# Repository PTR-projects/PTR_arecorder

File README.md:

# Arecorder - Open Source Flight Data Recorder

**Version:** v2.2 (PTR edition)  
**Maintained by:** bartekM  

A compact, high-g flight data recorder designed specifically for model and amateur rocketry. The Arecorder logs 3-axis acceleration and orientation data to an SD card during launch, ascent, apogee, and recovery. Developed and used by the **Polskie Towarzystwo Rakietowe (PTR)** – the Polish Rocketry Society.

This repository contains all **design files** needed to build your own Arecorder: KiCad schematics & PCB layout, Gerber files, Bill of Materials (BOM), assembly notes, and firmware source code.

- **Original forum thread** (Polish/English discussion): [forum.rakiety.org.pl/viewtopic.php?t=3039](https://forum.rakiety.org.pl/viewtopic.php?t=3039)
- **PTR Discord** (support & community)

---

## Features

- High-range 3-axis accelerometer:
  - Primary: **MMA6827** (±120 g)
  - Alternative: **H3LIS331** (with adapter board, higher availability and better specs)
- On-board SD card slot for raw flight data logging
- Improved firmware with better calibration accuracy and write reliability
- Compact design suitable for most model rockets (fits standard payload bays)
- Easy post-flight analysis (data saved in simple format)
- Open-source hardware & firmware – build it yourself or modify it

---

---

## Quick Start

1. **Order PCBs** – use the Gerbers in `hardware/gerbers/` (any PCB manufacturer, e.g. JLCPCB, PCBWay).
2. **Buy components** – see `hardware/BOM.csv`.
3. **Assemble** – most soldering can be done by hand; complex parts can be outsourced.
4. **Flash firmware** – use MPLAB X IDE + PIC debugger.
5. **Format SD card** (FAT32) before first use.
6. **Calibrate** the accelerometer (detailed in the manual).
7. **Fly** – insert into rocket, power on, launch, retrieve data after flight.

Full assembly and usage instructions are in the original manual and `docs/assembly-guide.md`.

---

## Hardware Notes (v2.2 PTR)

- Double-layer PCB (no changes planned for this revision)
- Sensor upgrade from original MMA6519 (80 g) to MMA6827 (120 g)
- Optional H3LIS331 adapter board included in the design files

---

## License

- **Hardware designs** – [CERN Open Hardware Licence Version 2 – Strongly Reciprocal](LICENSE_hardware)  
- **Firmware & software** – [MIT LICENSE](LICENSE)
- **Documentation** – CC-BY-SA 4.0

See [LICENSE](LICENSE) file for details.

---

## Contributing

Pull requests are welcome! Whether it's:
- Bug fixes
- New features
- Better documentation
- Improved firmware

Just open an issue or PR. You can also support development via [Buy Me a Coffee](https://www.buymeacoffee.com/bartekM).

---

## Contact

- Maintainer: **bartekM** (GitHub @bartekM or PM on PTR forum/Discord)
- Community: PTR Discord server

---

**Happy flying and safe recoveries!** 🚀

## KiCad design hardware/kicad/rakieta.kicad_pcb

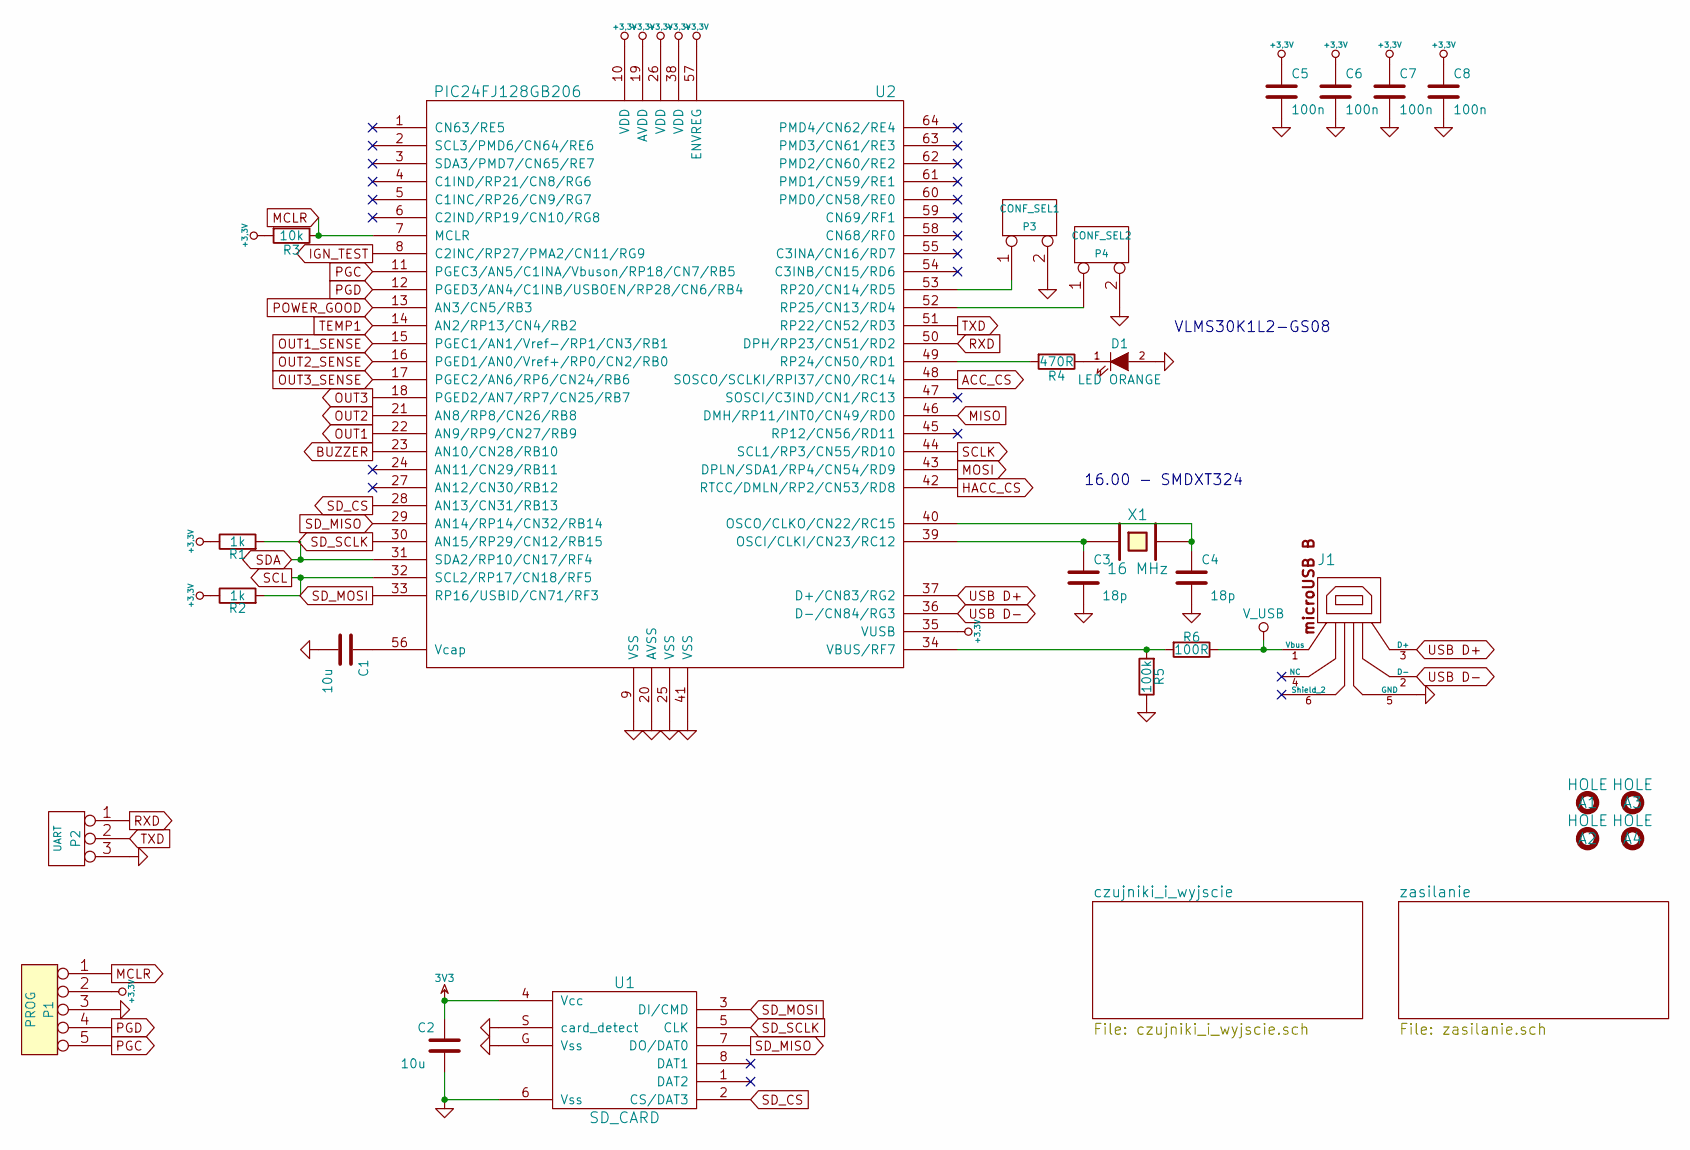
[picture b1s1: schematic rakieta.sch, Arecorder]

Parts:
A1, A2, A3, A4: HOLE; HOLE_3mm
C1, C2: 10u; SM0805
C3, C4: 18p; SM0603
C5, C6, C7, C8: 100n; SM0603
D1: LED ORANGE; SM1210_DIODE
J1: USB_B_micro; USB_MICRO
P1: PROG; conn_goldpin_5
P2: UART; conn_goldpin_3
P3: CONF_SEL1; conn_goldpin_2
P4: CONF_SEL2; conn_goldpin_2
R1, R2: 1k; SM0603
R3: 10k; SM0603
R4: 470R; SM0603
R5: 100k; SM0603
R6: 100R; SM0603
U1: SD_CARD; MICRO_SD_CARD_SLOT
U2: PIC24FJ128GB206; TQFP_64
X1: 16 MHz; HC-3.4x2.7

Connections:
3V3: C2.1, U1.4 (Vcc); also elsewhere on the board
+3.3V: C5.1, C6.1, C7.1, C8.1, P1.2, R1.1, R2.1, R3.2, U2.10 (VDD), U2.19 (AVDD), U2.26 (VDD), U2.35 (VUSB), U2.38 (VDD), U2.57 (ENVREG); also elsewhere on the board
ACC_CS: U2.48 (SOSCO/SCLKI/RPI37/CN0/RC14); also elsewhere on the board
BUZZER: U2.23 (AN10/CN28/RB10); also elsewhere on the board
GND: C1.2, C2.2, C3.2, C4.2, C5.2, C6.2, C7.2, C8.2, D1.2 (A), J1.5 (GND), P1.3, P2.3, P3.2 (PM), P4.2 (PM), R5.1, U1.6 (Vss), U1.G (Vss), U1.S (card_detect), U2.9 (VSS), U2.20 (AVSS), U2.25 (VSS), U2.41 (VSS); also elsewhere on the board
HACC_CS: U2.42 (RTCC/DMLN/RP2/CN53/RD8); also elsewhere on the board
IGN_TEST: U2.8 (C2INC/RP27/PMA2/CN11/RG9); also elsewhere on the board
MCLR: P1.1, R3.1, U2.7 (MCLR)
MISO: U2.46 (DMH/RP11/INT0/CN49/RD0); also elsewhere on the board
MOSI: U2.43 (DPLN/SDA1/RP4/CN54/RD9); also elsewhere on the board
unnamed: C1.1, U2.56 (Vcap)
unnamed: C3.1, U2.39 (OSCI/CLKI/CN23/RC12), X1.1
unnamed: C4.1, U2.40 (OSCO/CLKO/CN22/RC15), X1.2
unnamed: D1.1 (K), R4.1
unnamed: P3.1, U2.53 (RP20/CN14/RD5)
unnamed: P4.1, U2.52 (RP25/CN13/RD4)
unnamed: R4.2, U2.49 (RP24/CN50/RD1)
unnamed: R5.2, R6.2, U2.34 (VBUS/RF7)
OUT1: U2.22 (AN9/RP9/CN27/RB9); also elsewhere on the board
OUT1_SENSE: U2.15 (PGEC1/AN1/Vref-/RP1/CN3/RB1); also elsewhere on the board
OUT2: U2.21 (AN8/RP8/CN26/RB8); also elsewhere on the board
OUT2_SENSE: U2.16 (PGED1/AN0/Vref+/RP0/CN2/RB0); also elsewhere on the board
OUT3: U2.18 (PGED2/AN7/RP7/CN25/RB7); also elsewhere on the board
OUT3_SENSE: U2.17 (PGEC2/AN6/RP6/CN24/RB6); also elsewhere on the board
PGC: P1.5, U2.11 (PGEC3/AN5/C1INA/Vbuson/RP18/CN7/RB5)
PGD: P1.4, U2.12 (PGED3/AN4/C1INB/USBOEN/RP28/CN6/RB4)
POWER_GOOD: U2.13 (AN3/CN5/RB3); also elsewhere on the board
RXD: P2.1, U2.50 (DPH/RP23/CN51/RD2)
SCL: R2.2, U2.32 (SCL2/RP17/CN18/RF5); also elsewhere on the board
SCLK: U2.44 (SCL1/RP3/CN55/RD10); also elsewhere on the board
SDA: R1.2, U2.31 (SDA2/RP10/CN17/RF4); also elsewhere on the board
SD_CS: U1.2 (CS/DAT3), U2.28 (AN13/CN31/RB13)
SD_MISO: U1.7 (DO/DAT0), U2.29 (AN14/RP14/CN32/RB14)
SD_MOSI: U1.3 (DI/CMD), U2.33 (RP16/USBID/CN71/RF3)
SD_SCLK: U1.5 (CLK), U2.30 (AN15/RP29/CN12/RB15)
TEMP1: U2.14 (AN2/RP13/CN4/RB2); also elsewhere on the board
TXD: P2.2 (PM), U2.51 (RP22/CN52/RD3)
USB D+: J1.3 (D+), U2.37 (D+/CN83/RG2)
USB D-: J1.2 (D-), U2.36 (D-/CN84/RG3)
V_USB: J1.1 (Vbus), R6.1; also elsewhere on the board

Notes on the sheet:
16.00 - SMDXT324
VLMS30K1L2-GS08

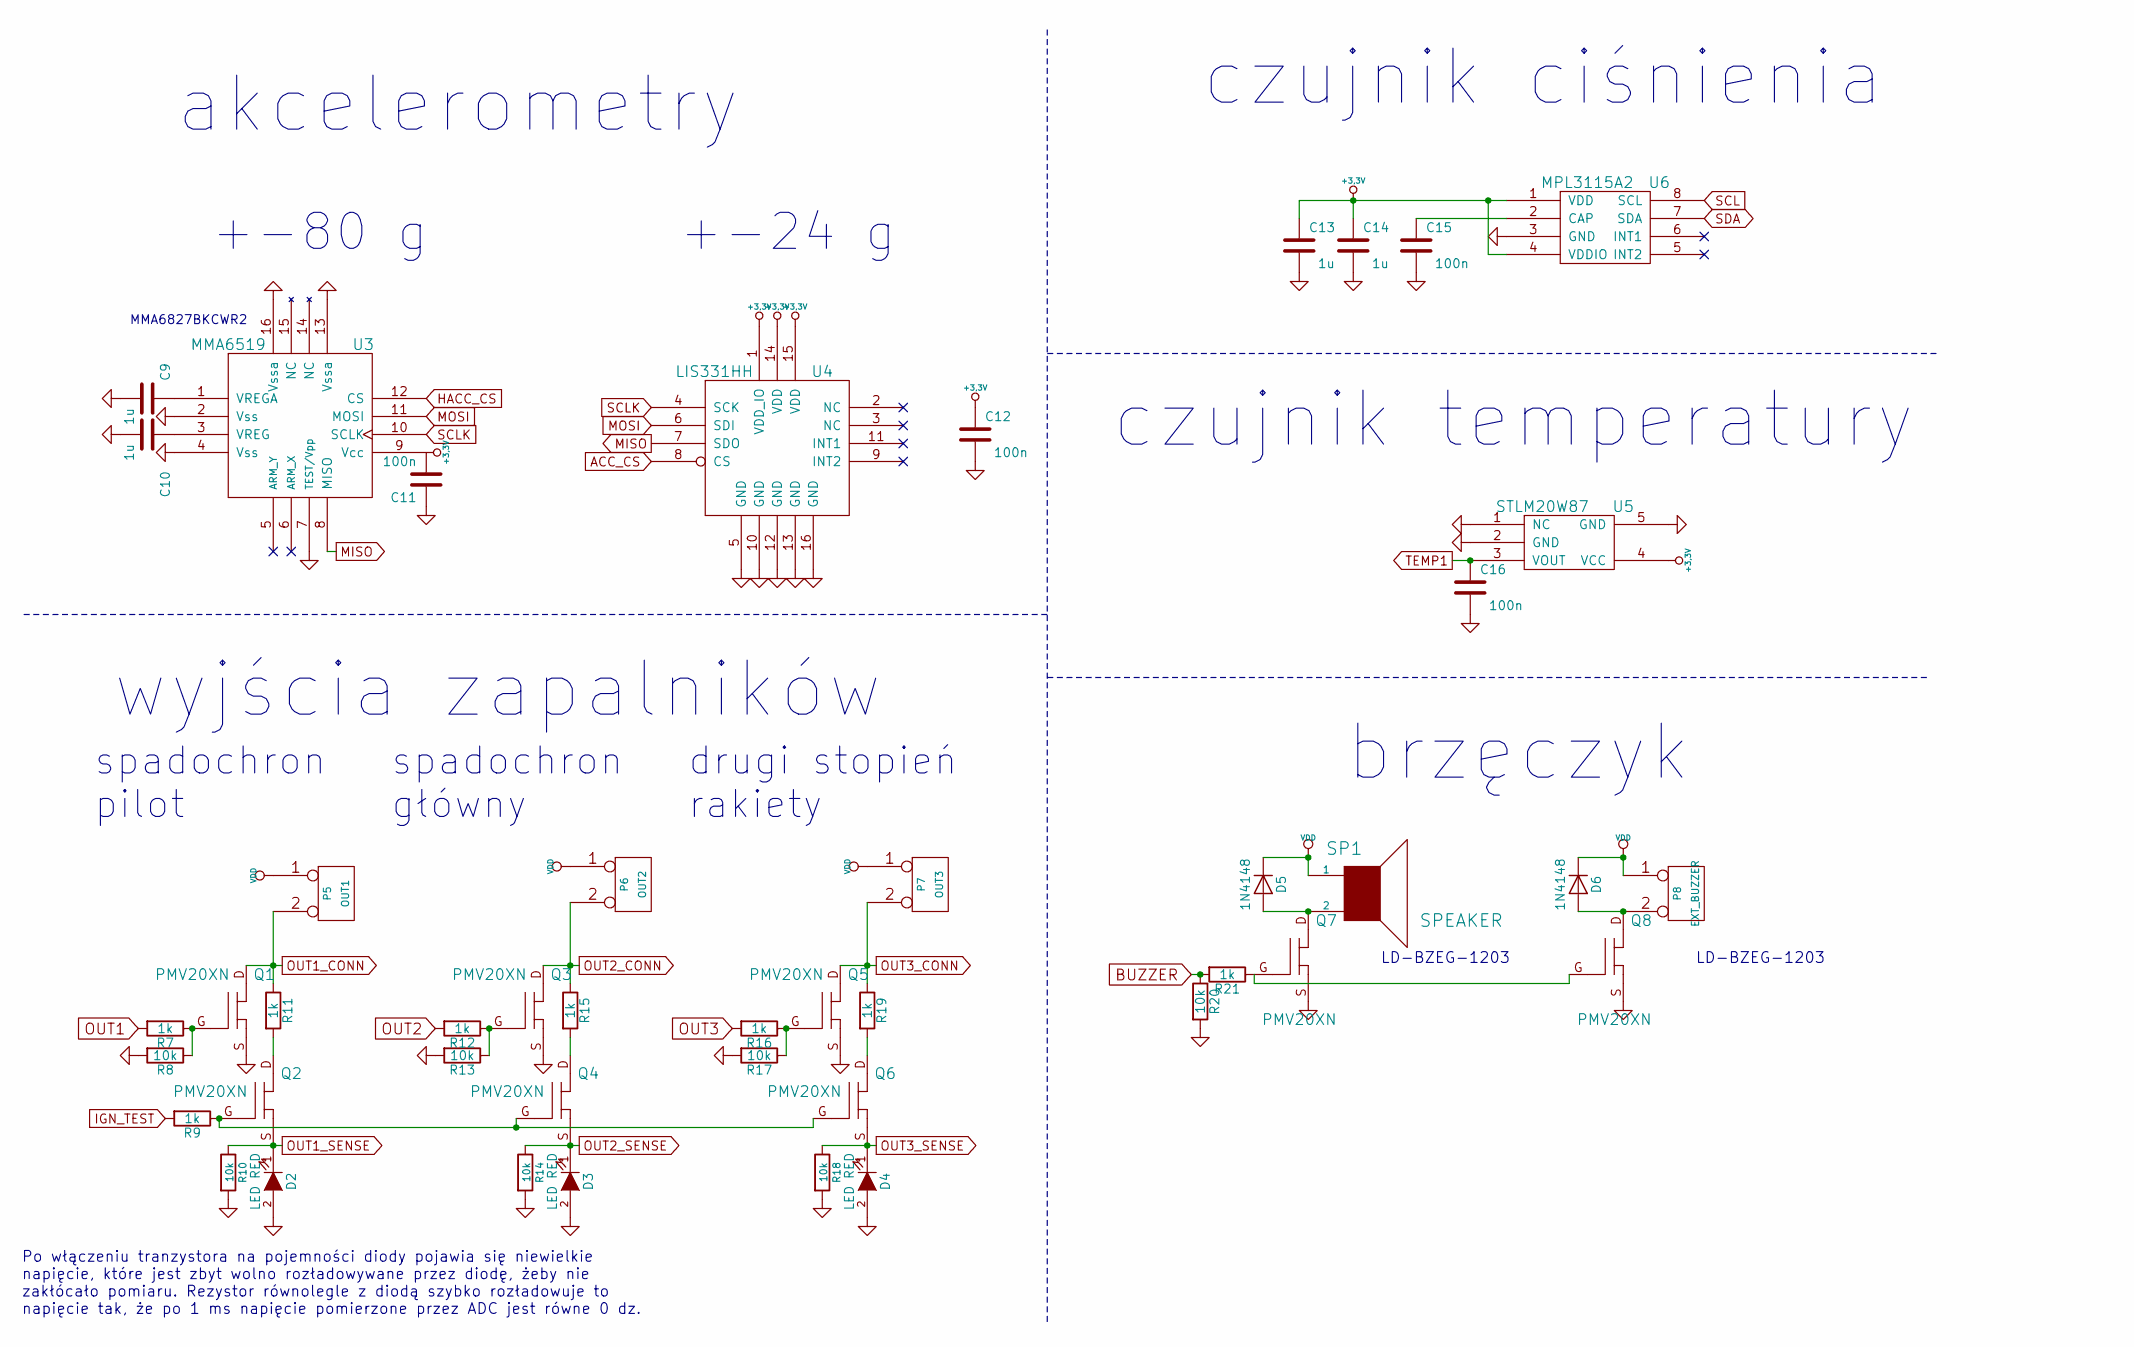
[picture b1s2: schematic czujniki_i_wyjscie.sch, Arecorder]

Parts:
C9, C10: 1u; SM0603
C11, C12, C16: 100n; SM0603
C13, C14: 1u; C_0603_1608Metric
C15: 100n; C_0603_1608Metric
D2, D3, D4: LED RED; SM1210_DIODE
D5, D6: 1N4148; SM0805_DIODE
P5: OUT1; conn_ark_2_3.81
P6: OUT2; conn_ark_2_3.81
P7: OUT3; conn_ark_2_3.81
P8: EXT_BUZZER; conn_goldpin_2
Q1, Q2, Q3, Q4, Q5, Q6, Q7, Q8: PMV20XN; SOT23GDS
R7, R9, R11, R12, R15, R16, R19, R21: 1k; SM0603
R8, R10, R13, R14, R17, R18, R20: 10k; SM0603
SP1: SPEAKER; buzzer_12mm
U3: MMA6519; QFN16
U4: LIS331HH; LGA16
U5: STLM20W87; SOT323-5L
U6: MPL3115A2; LGA8_3x5

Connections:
+3.3V: C11.2, C12.1, C13.1, C14.1, U3.9 (Vcc), U4.1 (VDD_IO), U4.14 (VDD), U4.15 (VDD), U5.4 (VCC), U6.1 (VDD), U6.4 (VDDIO); also elsewhere on the board
ACC_CS: U4.8 (CS); also elsewhere on the board
BUZZER: R20.1, R21.2; also elsewhere on the board
GND: C9.2, C10.2, C11.1, C12.2, C13.2, C14.2, C15.2, C16.2, D2.2 (A), D3.2 (A), D4.2 (A), Q1.S, Q3.S, Q5.S, Q7.S, Q8.S, R8.2, R10.2, R13.2, R14.2, R17.2, R18.2, R20.2, U3.2 (Vss), U3.4 (Vss), U3.7 (TEST/Vpp), U3.13 (Vssa), U3.16 (Vssa), U4.5 (GND), U4.10 (GND), U4.12 (GND), U4.13 (GND), U4.16 (GND), U5.1 (NC), U5.2 (GND), U5.5 (GND), U6.3 (GND); also elsewhere on the board
HACC_CS: U3.12 (CS); also elsewhere on the board
IGN_TEST: R9.2; also elsewhere on the board
MISO: U3.8 (MISO), U4.7 (SDO); also elsewhere on the board
MOSI: U3.11 (MOSI), U4.6 (SDI); also elsewhere on the board
unnamed: C9.1, U3.1 (VREGA)
unnamed: C10.1, U3.3 (VREG)
unnamed: C15.1, U6.2 (CAP)
unnamed: D5.2 (A), Q7.D, SP1.2
unnamed: D6.2 (A), P8.2 (PM), Q8.D
unnamed: Q1.G, R7.1, R8.1
unnamed: Q2.D, R11.2
unnamed: Q2.G, Q4.G, Q6.G, R9.1
unnamed: Q3.G, R12.1, R13.1
unnamed: Q4.D, R15.2
unnamed: Q5.G, R16.1, R17.1
unnamed: Q6.D, R19.2
unnamed: Q7.G, Q8.G, R21.1
OUT1: R7.2; also elsewhere on the board
OUT1_CONN: P5.2 (PM), Q1.D, R11.1
OUT1_SENSE: D2.1 (K), Q2.S, R10.1; also elsewhere on the board
OUT2: R12.2; also elsewhere on the board
OUT2_CONN: P6.2 (PM), Q3.D, R15.1
OUT2_SENSE: D3.1 (K), Q4.S, R14.1; also elsewhere on the board
OUT3: R16.2; also elsewhere on the board
OUT3_CONN: P7.2 (PM), Q5.D, R19.1
OUT3_SENSE: D4.1 (K), Q6.S, R18.1; also elsewhere on the board
SCL: U6.8 (SCL); also elsewhere on the board
SCLK: U3.10 (SCLK), U4.4 (SCK); also elsewhere on the board
SDA: U6.7 (SDA); also elsewhere on the board
TEMP1: C16.1, U5.3 (VOUT); also elsewhere on the board
VDD: D5.1 (K), D6.1 (K), P5.1, P6.1, P7.1, P8.1, SP1.1; also elsewhere on the board

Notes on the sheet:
drugi stopień rakiety
spadochron główny
spadochron pilot
brzęczyk
czujnik temperatury
czujnik ciśnienia
+-24 g
+-80 g
akcelerometry
wyjścia zapalników
LD-BZEG-1203
Po włączeniu tranzystora na pojemności diody pojawia się niewielkie napięcie, które jest zbyt wolno rozładowywane przez diodę, żeby nie zakłócało pomiaru. Rezystor równolegle z diodą szybko rozładowuje to napięcie tak, że po 1 ms napięcie pomierzone przez ADC jest równe 0 dz.
MMA6827BKCWR2

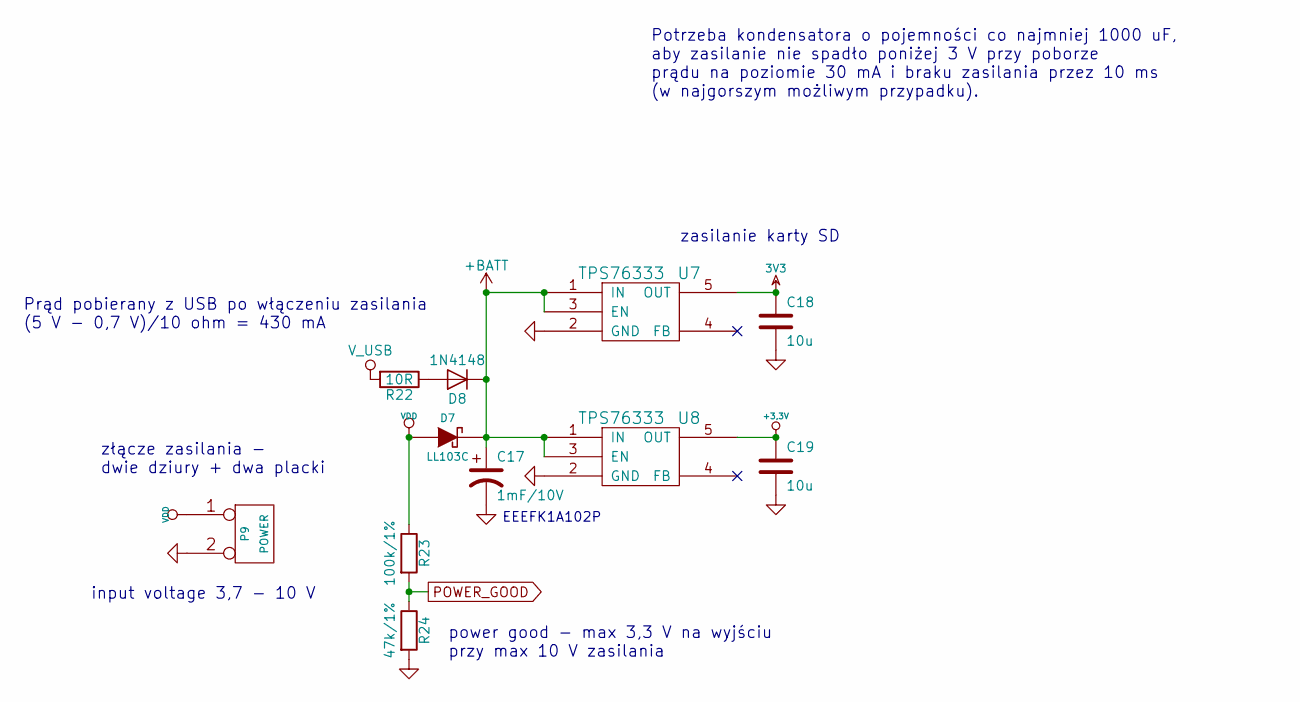
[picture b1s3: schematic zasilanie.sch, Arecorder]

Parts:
C17: 1mF/10V; SMD_G_cap
C18, C19: 10u; SM0805
D7: LL103C; SM1206_DIODE
D8: 1N4148; SM0805_DIODE
P9: POWER; conn_goldpin_2
R22: 10R; SM0603
R23: 100k/1%; SM0603
R24: 47k/1%; SM0603
U7, U8: TPS76333; SOT23-5

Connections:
3V3: C18.1, U7.5 (OUT); also elsewhere on the board
+3.3V: C19.1, U8.5 (OUT); also elsewhere on the board
+BATT: C17.1, D7.1 (K), D8.1 (K), U7.1 (IN), U7.3 (EN), U8.1 (IN), U8.3 (EN)
GND: C17.2, C18.2, C19.2, P9.2 (PM), R24.2, U7.2 (GND), U8.2 (GND); also elsewhere on the board
unnamed: D8.2 (A), R22.1
POWER_GOOD: R23.2, R24.1; also elsewhere on the board
VDD: D7.2 (A), P9.1, R23.1; also elsewhere on the board
V_USB: R22.2; also elsewhere on the board

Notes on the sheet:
zasilanie karty SD
Potrzeba kondensatora o pojemności co najmniej 1000 uF, aby zasilanie nie spadło poniżej 3 V przy poborze prądu na poziomie 30 mA i braku zasilania przez 10 ms (w najgorszym możliwym przypadku).
złącze zasilania - dwie dziury + dwa placki
input voltage 3,7 - 10 V
power good - max 3,3 V na wyjściu przy max 10 V zasilania
EEEFK1A102P
Prąd pobierany z USB po włączeniu zasilania (5 V - 0,7 V)/10 ohm = 430 mA

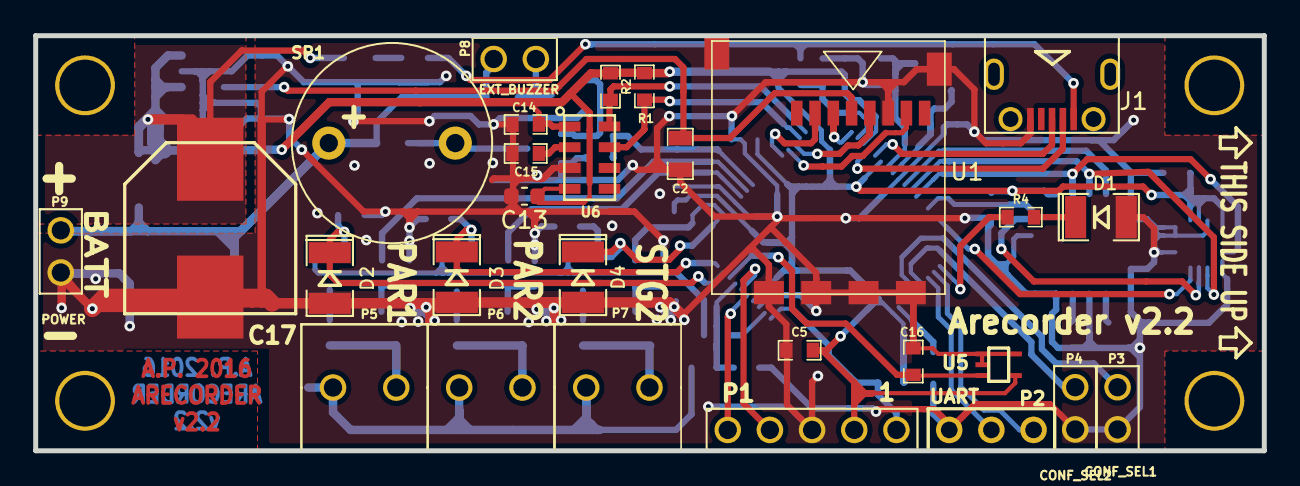
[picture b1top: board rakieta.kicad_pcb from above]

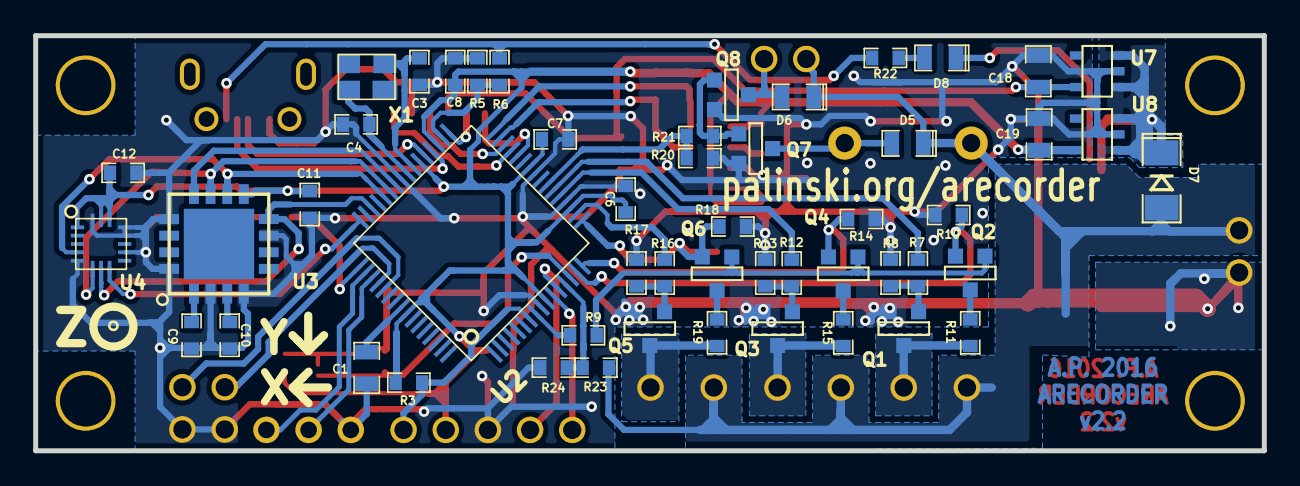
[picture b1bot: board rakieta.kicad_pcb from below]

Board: 2 copper layers, 74.0 x 25.0 mm, 83 parts (51 on the bottom side), 59 nets.

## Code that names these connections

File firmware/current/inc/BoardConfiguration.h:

#ifndef BOARD_CONFIGURATION_H
#define BOARD_CONFIGURATION_H

#define BOARD_2_2

#ifdef BOARD_2_2 // project date 2016.03.30
        // define I/O
        #define ACC_CS                  _LATC14
        #define TRIS_ACC_CS             _TRISC14
        #define HACC_CS                 _LATD8
        #define TRIS_HACC_CS            _TRISD8
        #define OUT1                    _LATB9
        #define OUT2                    _LATB8
        #define OUT3                    _LATB7
        #define TRIS_OUT1               _TRISB9
        #define TRIS_OUT2               _TRISB8
        #define TRIS_OUT3               _TRISB7
        #define BUZZER                  _LATB10
        #define TRIS_BUZZER             _TRISB10
        #define LED_RED                 _LATD1
        #define TRIS_LED                _TRISD1
        #define IGN_TEST                _LATG9
        #define TRIS_IGN_TEST           _TRISG9
        #define CONF_SEL1               _RD5
        #define CONF_SEL1_PUE           _CN14PUE
        #define CONF_SEL2               _RD4
        #define CONF_SEL2_PUE           _CN13PUE

        // define remappable pins
        #define RP_I_SPI_MISO           14
        #define RP_O_SPI_MOSI           _RP16R
        #define RP_O_SPI_SCK            _RP29R
        #define RP_I_SENSE_SPI_MISO     11
        #define RP_O_SENSE_SPI_MOSI     _RP4R
        #define RP_O_SENSE_SPI_SCK      _RP3R
        #define RP_I_UART_RX            23
        #define RP_O_UART_TX            _RP22R
        #define RP_O_PWM_1              _RP18R

#elif defined BOARD_2_0 // project date 2014.08.17
        // define I/O
        #define ACC_CS                  _LATC14
        #define TRIS_ACC_CS             _TRISC14
        #define HACC_CS                 _LATD8
        #define TRIS_HACC_CS            _TRISD8
        #define OUT1                    _LATB9
        #define OUT2                    _LATB8
        #define OUT3                    _LATB7
        #define TRIS_OUT1               _TRISB9
        #define TRIS_OUT2               _TRISB8
        #define TRIS_OUT3               _TRISB7
        #define BUZZER                  _LATB10
        #define TRIS_BUZZER             _TRISB10
        #define LED_RED                 _LATD1
        #define TRIS_LED                _TRISD1
        #define IGN_TEST                _LATG9
        #define TRIS_IGN_TEST           _TRISG9
        #define CONF_SEL1               _RD5
        #define CONF_SEL1_PUE           _CN14PUE
        #define CONF_SEL2               _RD4
        #define CONF_SEL2_PUE           _CN13PUE

        // define remappable pins
        #define RP_I_SPI_MISO           14
        #define RP_O_SPI_MOSI           _RP16R
        #define RP_O_SPI_SCK            _RP29R
        #define RP_I_SENSE_SPI_MISO     11
        #define RP_O_SENSE_SPI_MOSI     _RP4R
        #define RP_O_SENSE_SPI_SCK      _RP3R
        #define RP_I_UART_RX            23
        #define RP_O_UART_TX            _RP22R

#elif defined BOARD_0_9 // project date 2013.08.12
        // define I/O
        #define ACC_CS                  _LATB13
        #define TRIS_ACC_CS             _TRISB13
        #define HACC_CS                 _LATB12
        #define TRIS_HACC_CS            _TRISB12
        #define OUT1                    _LATA4
        #define OUT2                    _LATB4
        #define OUT3                    _LATA8
        #define TRIS_OUT1               _TRISA4
        #define TRIS_OUT2               _TRISB4
        #define TRIS_OUT3               _TRISA8
        #define BUZZER                  _LATA9
        #define TRIS_BUZZER             _TRISA9
        #define LED_RED                 _LATA10
        #define TRIS_LED                _TRISA10
        #define IGN_TEST                _LATB3
        #define TRIS_IGN_TEST           _TRISB3
        #define CONF_SEL1               _RC5
        #define CONF_SEL1_PUE           _CN26PUE
        #define CONF_SEL2               _RC4
        #define CONF_SEL2_PUE           _CN25PUE
        
        // define remappable pins
        #define RP_I_SPI_MISO           22
        #define RP_O_SPI_MOSI           _RP24R
        #define RP_O_SPI_SCK            _RP23R
        #define RP_I_UART_RX            1
        #define RP_O_UART_TX            _RP0R

#elif defined BOARD_0_8 // project date 2013.06.24
        // define I/O
        #define ACC_CS                  _LATB13
        #define TRIS_ACC_CS             _TRISB13
        #define HACC_CS                 _LATB12
        #define TRIS_HACC_CS            _TRISB12
        #define OUT1                    _LATA4
        #define OUT2                    _LATB4
        #define OUT3                    _LATA8
        #define TRIS_OUT1               _TRISA4
        #define TRIS_OUT2               _TRISB4
        #define TRIS_OUT3               _TRISA8
        #define BUZZER                  _LATA9
        #define TRIS_BUZZER             _TRISA9
        #define LED_RED                 _LATA10
        #define TRIS_LED                _TRISA10
        #define IGN_TEST                _LATB3
        #define TRIS_IGN_TEST           _TRISB3
        #define CONF_SEL1               _RC5
        #define CONF_SEL1_PUE           _CN26PUE
        #define CONF_SEL2               _RC4
        #define CONF_SEL2_PUE           _CN25PUE
        
        // define remappable pins
        #define RP_I_SPI_MISO           22
        #define RP_O_SPI_MOSI           _RP24R
        #define RP_O_SPI_SCK            _RP23R
        #define RP_I_UART_RX            1
        #define RP_O_UART_TX            _RP0R

#elif defined BOARD_0_7        // project date 2012.03.11
        // define I/O
        #define ACC_CS                  _LATA10
        #define TRIS_ACC_CS             _TRISA10
        #define HACC_CS                 _LATA7
        #define TRIS_HACC_CS            _TRISA7
        #define OUT1                    _LATC3
        #define OUT2                    _LATA9
        #define OUT3                    _LATB4
        #define TRIS_OUT1               _TRISC3
        #define TRIS_OUT2               _TRISA9
        #define TRIS_OUT3               _TRISB4
        #define BUZZER                  _LATB12
        #define TRIS_BUZZER             _TRISB12
        #define LED_RED                 _LATA8
        #define TRIS_LED                _TRISA8
        #define IGN_TEST                _LATA4
        #define TRIS_IGN_TEST           _TRISA4
        
        // define remappable pins
        #define RP_I_SPI_MISO           22
        #define RP_O_SPI_MOSI           _RP24R
        #define RP_O_SPI_SCK            _RP23R
        #define RP_I_UART_RX            11
        #define RP_O_UART_TX            _RP10R

#endif

#endif
